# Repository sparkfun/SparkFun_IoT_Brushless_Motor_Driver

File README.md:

SparkFun IoT Brushless Motor Driver (ESP32 WROOM, TMC6300)
========================================

[*SparkFun IoT Brushless Motor Driver (ESP32 WROOM, TMC6300) (ROB-22132)*](https://www.sparkfun.com/products/22132)

The SparkFun IoT Brushless Motor Driver is an all-in-one development platform. It includes all the components to create a simple IoT device or learn about [control systems](https://en.wikipedia.org/wiki/Control_system). On the boaard, users will find an ESP32 microcontroller, a TMC6300 motor driver, a [gimbal motor](https://www.sparkfun.com/products/20441), a TMAG5273 hall-effect sensor, three INA240A1 inline current sensors, an MCP6021T low-side current sensor, two user buttons, a Qwiic connector, a 3-pin JST connector (for the gimbal motor), and a WS2812 RGB LED.

The TMC6300 from [ADI + Trinamic](https://www.trinamic.com/) is a powerful and easy-to-use three-phase motor driver with up to 2A (1.4A<sub>RMS</sub>) of total drive current. Separate high-side and low-side control of the three half-bridges allows for incredible control of each phase of the [motor commutation](https://fab.cba.mit.edu/classes/865.21/topics/power_electronics/commutation/#bldc-commutation). We've found the [*Arduino Simple Field Oriented Control*](https://docs.simplefoc.com/) library to work well with the TMC6300 motor driver.

However, a field-oriented control (FOC) algorithm requires some feedback to close and optimize the control loop. Therefore, we integrated a TMAG5273 hall-effect sensor and INA240A1 current sensor amplifiers *(both manufactured by [Texas Instruments](https://www.ti.com/))* into the design of the IoT motor driver board. This allows users to incorporate a [position sensor](https://docs.simplefoc.com/position_sensors) and [current sensing](https://docs.simplefoc.com/current_sense) into the FOC algorithm or any feedback control loop they choose to implement.

Repository Contents
-------------------

* **[/docs](/docs/)** - Online documentation files
    * [assets](/docs/assets/) - Assets files
        * [arduino_examples](/docs/assets/arduino_examples/) - Example code
        * [board_files](/docs/assets/board_files/) - Files for the product design
            * [Eagle design files](/docs/assets/board_files/eagle_files.zip) (.zip)
            * [Schematic](/docs/assets/board_files/schematic.pdf) (.pdf)
            * [Dimensions](/docs/assets/board_files/dimensions.pdf) (.pdf)
        * [component_documentation](/docs/assets/component_documentation/) - Datasheets for hardware components
        * [img/hookup_guide/](/docs/assets/img/hookup_guide/) - Images for hookup guide documentation
* **[/Hardware](/Hardware/)** - Eagle design files (.brd, .sch)
* **[/Production](/Production/)** - Production files

Documentation
--------------

* **[Hookup Guide (mkdocs)](http://docs.sparkfun.com/SparkFun_IoT_Brushless_Motor_Driver/)** - Hookup guide for the IoT Brushless Motor Driver hosted by GitHub pages.

*Need to download or print our hookup guide?*

* [Print *(Print to PDF)* from Single-Page View](http://docs.sparkfun.com/SparkFun_IoT_Brushless_Motor_Driver/print_view)

Product Variants
----------------

* [ROB-22132](https://www.sparkfun.com/products/22132)- v1.0, Initial Release

Version History
---------------

* [v10](https://github.com/sparkfun/SparkFun_IoT_Brushless_Motor_Driver/releases/tag/v10) - Initial Release

License Information
-------------------

This product is ***open source***!

Please review the [`LICENSE.md`](./LICENSE.md) file for license information.

If you have any questions or concerns about licensing, please contact technical support on our [SparkFun forums](https://forum.sparkfun.com/viewforum.php?f=152).

Distributed as-is; no warranty is given.

- Your friends at SparkFun.

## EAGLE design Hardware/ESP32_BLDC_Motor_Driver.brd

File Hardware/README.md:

SparkFun IoT Brushless Motor Driver Design Files
=====================================

The .sch and .brd files hare are Eagle CAD schematic and PCB design files from SparkFun Electronics.
A freeware version of Autodesk Eagle can be found [here](https://www.autodesk.com/products/eagle/free-download).

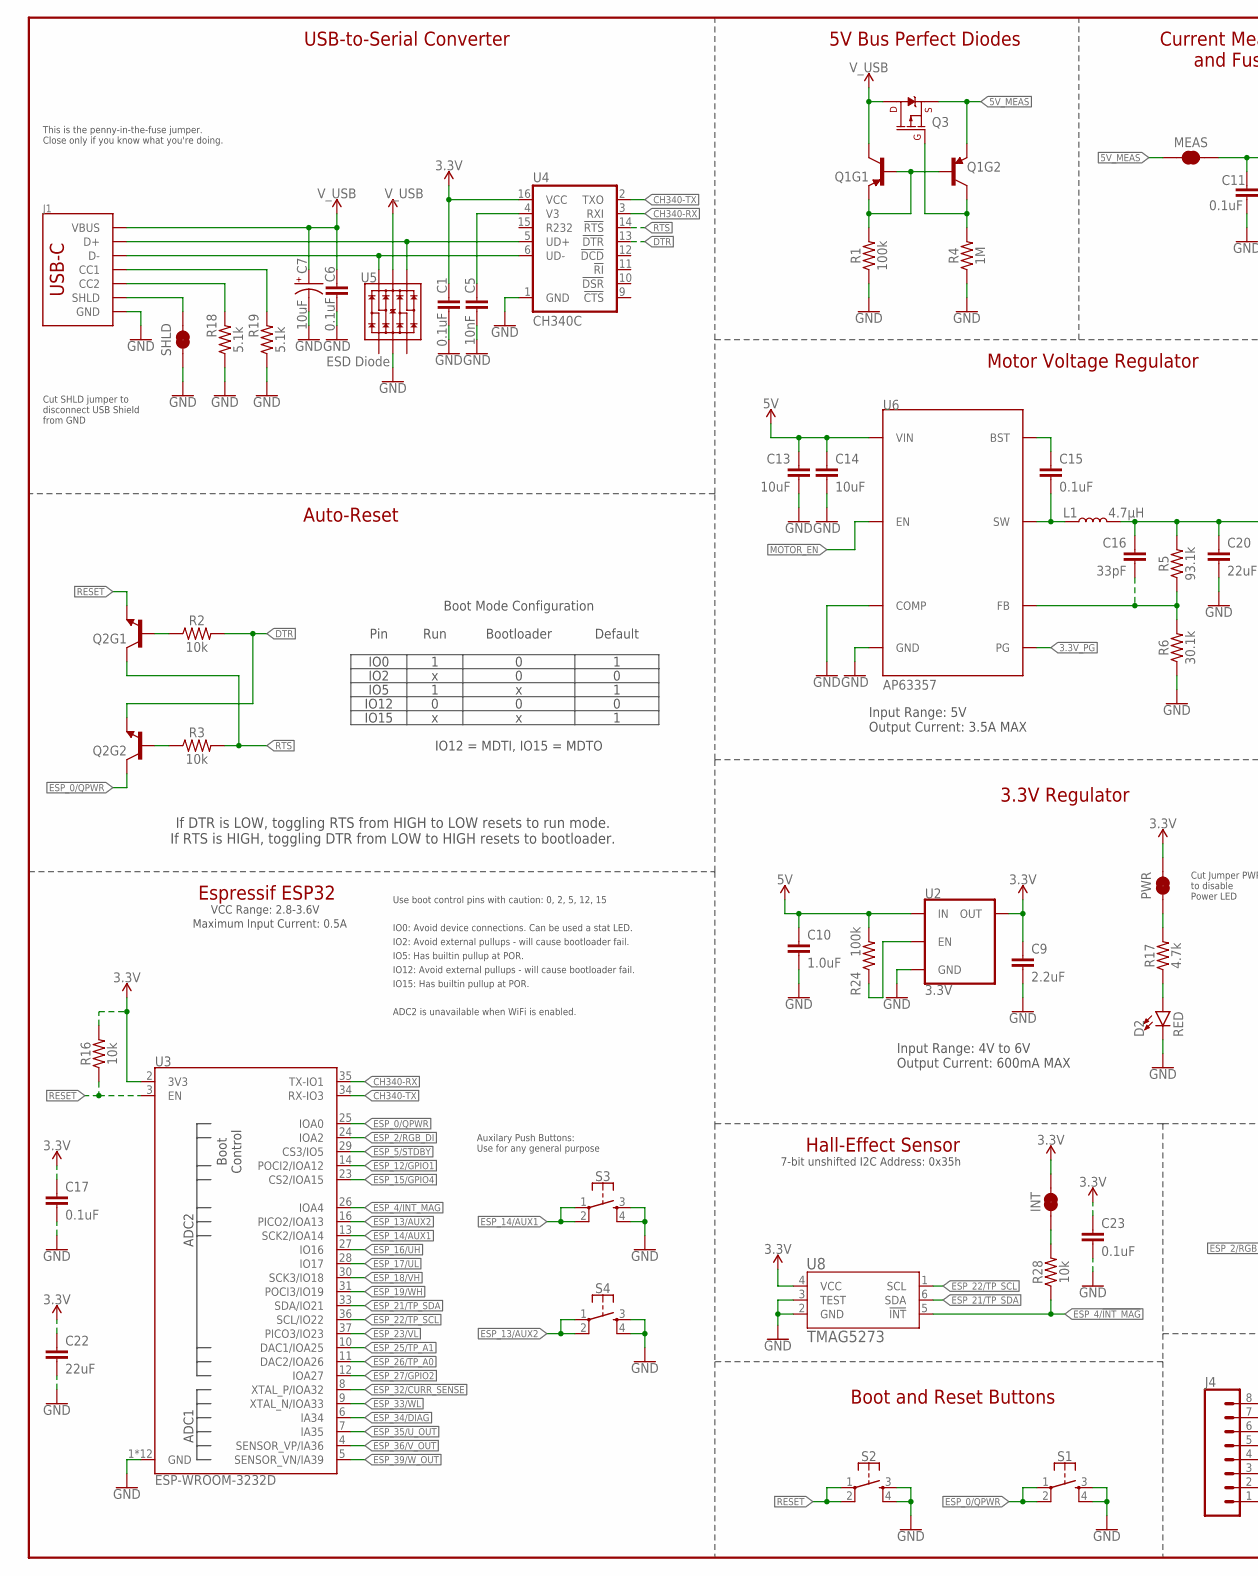
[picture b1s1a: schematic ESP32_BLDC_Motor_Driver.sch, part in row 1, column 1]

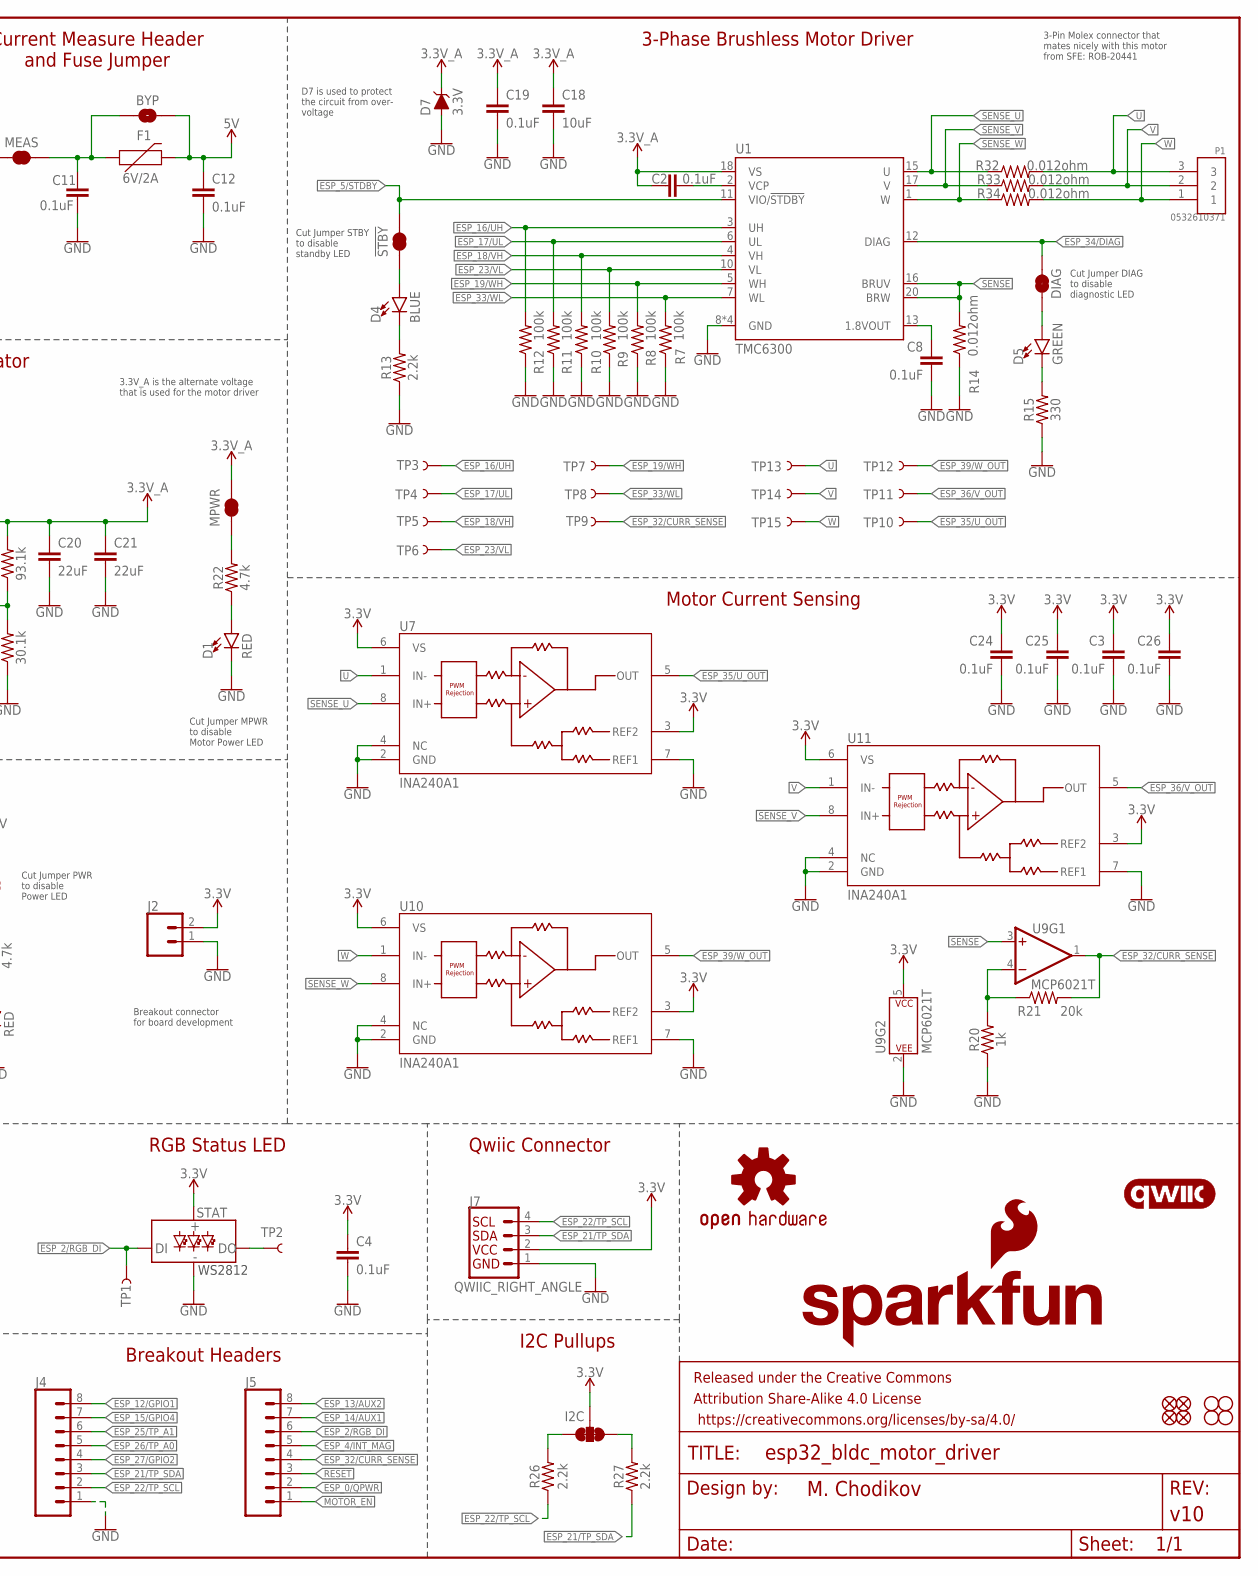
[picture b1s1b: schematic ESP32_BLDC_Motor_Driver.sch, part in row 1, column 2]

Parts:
!STBY: JUMPER-SMT_2_NC_TRACE_SILK; SMT-JUMPER_2_NC_TRACE_SILK
BYP: JUMPER-SMT_2_NO_SILK; SMT-JUMPER_2_NO_SILK
C1, C2, C3, C4, C6, C8, C11, C12, C15, C17, C19, C24, C25, C26: 0.1uF; 0603
C5: 10nF; 0603
C7: 10uF; 0603-POLAR
C9: 2.2uF; 0603
C10: 1.0uF; 0603
C13, C14, C18: 10uF; 0603
C16: 33pF; 0603
C20, C21, C22: 22uF; 0603
C23: 0.1uF; 0402
D1, D2: RED; LED-0603
D4: BLUE; LED-0603
D5: GREEN; LED-0603
D7: 3.3V; SOD-323
DIAG: JUMPER-SMT_2_NC_TRACE_SILK; SMT-JUMPER_2_NC_TRACE_SILK
F1: 6V/2A; 1210
FD1, FD2, FD3, FD4: FIDUCIALUFIDUCIAL; FIDUCIAL-MICRO
FRAME1: FRAME-LEDGER; CREATIVE_COMMONS
H1, H2, H3, H4: STAND-OFF
I2C: JUMPER-SMT_3_2-NC_TRACE_SILK; SMT-JUMPER_3_2-NC_TRACE_SILK
INT: JUMPER-SMT_2_NC_TRACE_SILK; SMT-JUMPER_2_NC_TRACE_SILK
J1: USB-C Connector; USB-C-16P_4LAYER-PADS
J2: CONN_021X02_NO_SILK; 1X02_NO_SILK
J4: Breadboard Connector; 1X08_NO_SILK
J5: Breadboard Headers; 1X08_NO_SILK
J7: QWIIC_RIGHT_ANGLE; JST04_1MM_RA
L1: 4.7μH; INDUCTOR_4X4MM
LOGO1: SFE_LOGO_NAMEBLANK; BLANK
LOGO2: OSHW-LOGOM; OSHW-LOGO-M
LOGO3: SFE_LOGO_FLAME.2_INCH; SFE_LOGO_FLAME_.2
LOGO4: QWIIC_LOGO_5MM; QWIIC_5MM
MEAS: JUMPER-COMBO_2_NC_TRACE; COMBO-JUMPER_2_NC_TRACE
MPWR: JUMPER-SMT_2_NC_TRACE_SILK; SMT-JUMPER_2_NC_TRACE_SILK
P1: 0532610371; MOLEX_0532610371
PWR: JUMPER-SMT_2_NC_TRACE_SILK; SMT-JUMPER_2_NC_TRACE_SILK
Q1: TRANS_PNP_DUALSOT-363; SOT363_PHILIPS
Q2: NPN Transistors; SC70-6
Q3: 20V/4.2A/52mΩ/1.4W; SOT23-3
R1, R7, R8, R9, R10, R11, R12, R24: 100k; 0603
R2, R3, R16, R28: 10k; 0603
R4: 1M; 0603
R5: 93.1k; 0603
R6: 30.1k; 0603
R13, R26, R27: 2.2k; 0603
R14, R32, R33, R34: 0.012ohm; 0603
R15: 330; 0603
R17, R22: 4.7k; 0603
R18, R19: 5.1k; 0603
R20: 1k; 0603
R21: 20k; 0603
S1, S2, S3, S4: MOMENTARY-SWITCH-SPST-2-SMD-5.2MM-TALL; TACTILE_SWITCH_SMD_5.2MM
SHLD: JUMPER-SMT_2_NC_TRACE_SILK; SMT-JUMPER_2_NC_TRACE_SILK
STAT: WS2812_2020; WS2812-2020
TP1, TP2, TP3, TP4, TP5, TP6, TP7, TP8, TP9, TP10, TP11, TP12, TP13, TP14, TP15: TEST-POINT3X4; PAD.03X.04
U1: TMC6300; QFN-20
U2: 3.3V; SOT23-5
U3: ESP-WROOM-3232D; ESP-WROOM-32D
U4: CH340C; SO016
U5: ESD Diode; SOT-23-6
U6: AP63357; V-DFN3020-13
U7, U10, U11: INA240A1; D8_TEX
U8: TMAG5273; SOT23-6_DBV_TEX
U9: MCP6021T; SOT23-5

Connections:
1.8_VOUT: C8.1, U1.13 (1.8VOUT)
3.3V: C1.1, C3.1, C4.1, C9.1, C17.1, C22.1, C23.1, C24.1, C25.1, C26.1, I2C.2, INT.2, J2.2, J7.2, PWR.2, R16.2, STAT.VCC, U2.5 (OUT), U3.2 (3V3), U4.16 (VCC), U7.3 (REF2), U7.6 (VS), U8.4 (VCC), U9.5 (P$V+), U10.3 (REF2), U10.6 (VS), U11.3 (REF2), U11.6 (VS)
3.3V_A: C2.1, C16.2, C18.1, C19.1, C20.1, C21.1, D7.C, L1.P$2 (2), MPWR.2, R5.2, U1.18 (VS)
3.3V_PG: U6.P$5 (PG)
5V: BYP.2, C10.1, C12.1, C13.1, C14.1, F1.2, R24.2, U2.1 (IN), U6.P$1 (VIN)
5V_MEAS: MEAS.1, MEAS.3 (1), Q1.4 (E), Q3.2 (S)
!RESET: J5.3, Q2.4 (E), R16.1, S2.1, S2.2, U3.3 (EN)
BST: C15.1, U6.P$6 (BST)
CH340-RX: U3.35 (TX-IO1), U4.3 (RXI)
CH340-TX: U3.34 (RX-IO3), U4.2 (TXO)
D: D5.A, DIAG.1
D+: J1.A6 (D+), J1.B6 (D+), U4.5 (UD+), U5.4 (IO3)
D-: J1.A7 (D-), J1.B7 (D-), U4.6 (UD-), U5.6 (IO4)
DTR: Q2.1 (E), R2.2, U4.13 (!DTR)
ESP_0/QPWR: J5.2, Q2.6 (C), S1.1, S1.2, U3.25 (IOA0)
ESP_2/RGB_DI: J5.6, STAT.DI, TP1.1, U3.24 (IOA2)
ESP_4/!INT_MAG: J5.5, R28.1, U3.26 (IOA4), U8.5 (!INT)
ESP_5/!STDBY: !STBY.2, U1.11 (VIO/!STDBY!), U3.29 (CS3/IO5)
ESP_12/GPIO1: J4.8, U3.14 (POCI2/IOA12)
ESP_13/AUX2: J5.8, S4.1, S4.2, U3.16 (PICO2/IOA13)
ESP_14/AUX1: J5.7, S3.1, S3.2, U3.13 (SCK2/IOA14)
ESP_15/GPIO4: J4.7, U3.23 (CS2/IOA15)
ESP_16/UH: R12.2, TP3.1, U1.3 (UH), U3.27 (IO16)
ESP_17/UL: R11.2, TP4.1, U1.6 (UL), U3.28 (IO17)
ESP_18/VH: R10.2, TP5.1, U1.4 (VH), U3.30 (SCK3/IO18)
ESP_19/WH: R8.2, TP7.1, U1.5 (WH), U3.31 (POCI3/IO19)
ESP_21/TP_SDA: J4.3, J7.3, R27.1, U3.33 (SDA/IO21), U8.6 (SDA)
ESP_22/TP_SCL: J4.2, J7.4, R26.1, U3.36 (SCL/IO22), U8.1 (SCL)
ESP_23/VL: R9.2, TP6.1, U1.10 (VL), U3.37 (PICO3/IO23)
ESP_25/TP_A1: J4.6, U3.10 (DAC1/IOA25)
ESP_26/TP_A0: J4.5, U3.11 (DAC2/IOA26)
ESP_27/GPIO2: J4.4, U3.12 (IOA27)
ESP_32/CURR_SENSE: J5.4, R21.2, TP9.1, U3.8 (XTAL_P/IOA32), U9.1 (OUT)
ESP_33/WL: R7.2, TP8.1, U1.7 (WL), U3.9 (XTAL_N/IOA33)
ESP_34/DIAG: DIAG.2, U1.12 (DIAG), U3.6 (IA34)
ESP_35/U_OUT: TP10.1, U3.7 (IA35), U7.5 (OUT)
ESP_36/V_OUT: TP11.1, U3.4 (SENSOR_VP/IA36), U11.5 (OUT)
ESP_39/W_OUT: TP12.1, U3.5 (SENSOR_VN/IA39), U10.5 (OUT)
FB: C16.1, R5.1, R6.2, U6.P$3 (FB)
GND: C1.2, C3.2, C4.2, C5.2, C6.2, C7.-, C8.2, C9.2, C10.2, C11.2, C12.2, C13.2, C14.2, C17.2, C18.2, C19.2, C20.2, C21.2, C22.2, C23.2, C24.2, C25.2, C26.2, D1.C, D2.C, D7.A, J1.GND, J1.GND2 (GND), J2.1, J4.1, J7.1, R1.1, R4.1, R6.1, R7.1, R8.1, R9.1, R10.1, R11.1, R12.1, R13.1, R14.1, R15.1, R18.1, R19.1, R20.1, S1.3, S1.4, S2.3, S2.4, S3.3, S3.4, S4.3, S4.4, SHLD.1, STAT.GND, U1.8 (GND), U1.9 (GND), U1.14 (GND), U1.PAD (GND), U2.2 (GND), U3.1 (GND), U3.15 (GND), U3.38 (GND), U3.GND, U3.GNDT1 (GND), U3.GNDT2 (GND), U3.GNDT3 (GND), U3.GNDT4 (GND), U3.GNDT5 (GND), U3.GNDT6 (GND), U3.GNDT7 (GND), U3.GNDT8 (GND), U4.1 (GND), U5.2 (VSS), U6.P$4 (COMP), U6.P$8 (GND), U7.2 (GND), U7.4 (NC), U7.7 (REF1), U8.2 (GND), U8.3 (TEST), U9.2 (P$V-), U10.2 (GND), U10.4 (NC), U10.7 (REF1), U11.2 (GND), U11.4 (NC), U11.7 (REF1)
MOTOR_EN: J5.1, U6.P$2 (EN)
unnamed: J1.A5 (CC1), R19.2
unnamed: C5.1, U4.4 (V3)
unnamed: J1.B5 (CC2), R18.2
unnamed: C2.2, U1.2 (VCP)
unnamed: R24.1, U2.3 (EN)
unnamed: Q2.5 (B), R2.1
unnamed: Q2.2 (B), R3.1
unnamed: D2.A, R17.1
unnamed: INT.1, R28.2
unnamed: I2C.3, R26.2
unnamed: I2C.1, R27.2
unnamed: R20.2, R21.1, U9.4 (-IN)
unnamed: PWR.1, R17.2
unnamed: BYP.1, C11.1, F1.1, MEAS.2, MEAS.4 (2)
unnamed: Q1.3 (C), Q3.1 (G), R4.2
unnamed: Q1.1 (E), Q1.2 (B), Q1.5 (B), R1.2
unnamed: D1.A, R22.1
unnamed: MPWR.1, R22.2
unnamed: D4.C, R13.2
unnamed: D5.C, R15.2
RTS: Q2.3 (C), R3.2, U4.14 (!RTS)
S: !STBY.1, D4.A
SENSE: R14.2, U1.16 (BRUV), U1.20 (BRW), U9.3 (+IN)
SENSE_U: R32.1, U1.15 (U), U7.8 (IN+)
SENSE_V: R33.1, U1.17 (V), U11.8 (IN+)
SENSE_W: R34.1, U1.1 (W), U10.8 (IN+)
SHLD: J1.SHLD1 (SHLD), J1.SHLD2 (SHLD), J1.SHLD3 (SHLD), J1.SHLD4 (SHLD), SHLD.2
SW: C15.2, L1.P$1 (1), U6.P$7 (SW), U6.P$9 (SW)
TP2: STAT.DO, TP2.1
U: P1.3, R32.2, TP13.1, U7.1 (IN-)
V: P1.2, R33.2, TP14.1, U11.1 (IN-)
V_USB: C6.1, C7.+, J1.VBUS1 (VBUS), J1.VBUS2 (VBUS), Q1.6 (C), Q3.3 (D), U5.5 (VCC)
W: P1.1, R34.2, TP15.1, U10.1 (IN-)

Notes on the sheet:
Espressif ESP32
VCC Range: 2.8-3.6V
3-Phase Brushless Motor Driver
USB-to-Serial Converter
Cut Jumper DIAG to disable diagnostic LED
Cut Jumper STBY to disable standby LED
Breakout Headers
Auto-Reset
Boot and Reset Buttons
If DTR is LOW, toggling RTS from HIGH to LOW resets to run mode. If RTS is HIGH, toggling DTR from LOW to HIGH resets to bootloader.
3.3V Regulator
3-Pin Molex connector that mates nicely with this motor from SFE: ROB-20441
Cut SHLD jumper to disconnect USB Shield from GND
This is the penny-in-the-fuse jumper. Close only if you know what you're doing.
Pin
IO0
IO2
IO12
IO15
IO5
Run
Bootloader
Default
IO12 = MDTI, IO15 = MDTO
Boot Mode Configuration
RGB Status LED
IO0: Avoid device connections. Can be used a stat LED.
ADC2 is unavailable when WiFi is enabled.
IO12: Avoid external pullups - will cause bootloader fail.
Use boot control pins with caution: 0, 2, 5, 12, 15
IO2: Avoid external pullups - will cause bootloader fail.
IO15: Has builtin pullup at POR.
IO5: Has builtin pullup at POR.
Qwiic Connector
Auxilary Push Buttons: Use for any general purpose
WS2812
Hall-Effect Sensor
Maximum Input Current: 0.5A
7-bit unshifted I2C Address: 0x35h
D7 is used to protect the circuit from over- voltage

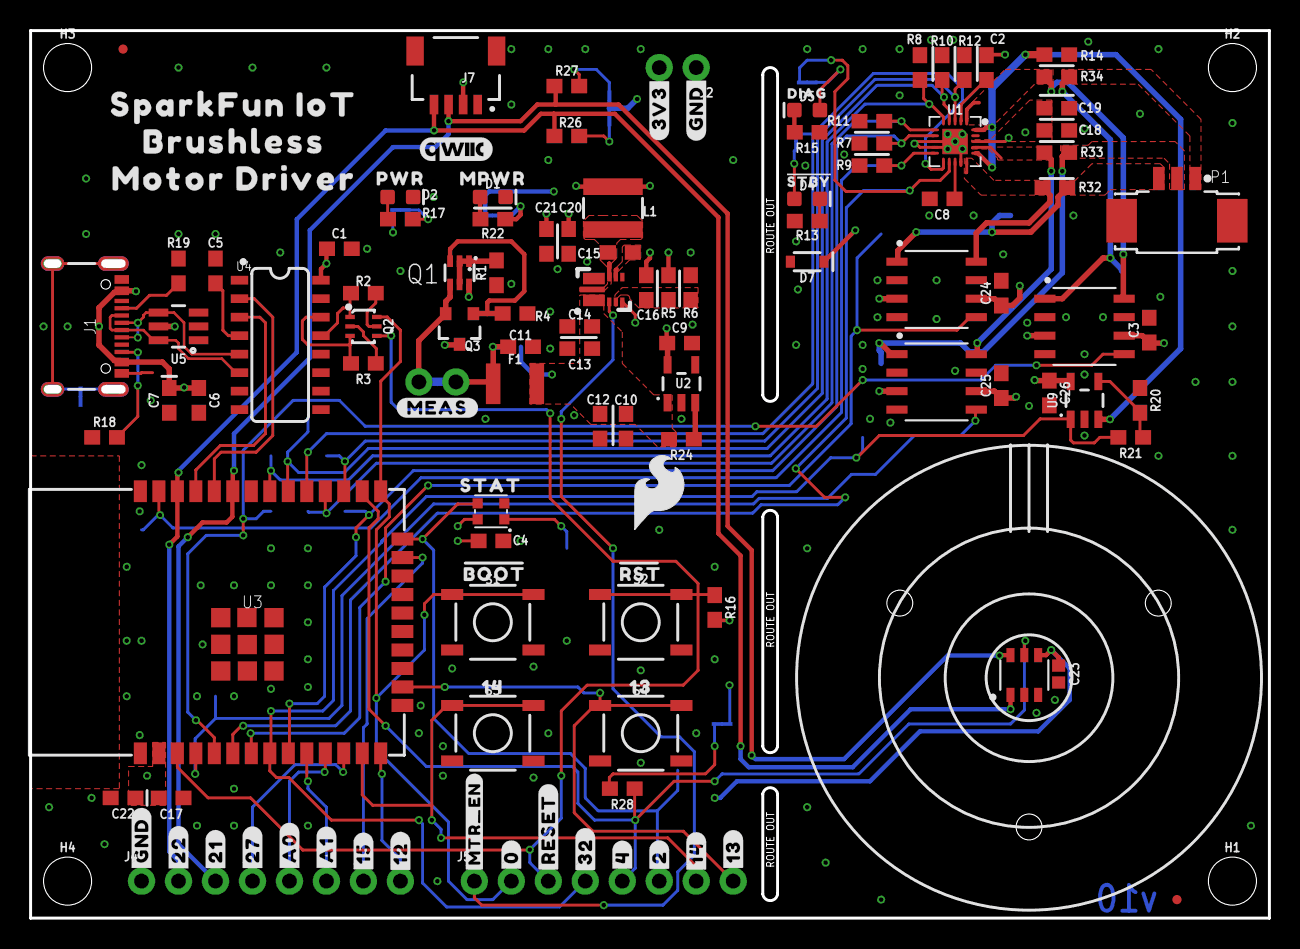
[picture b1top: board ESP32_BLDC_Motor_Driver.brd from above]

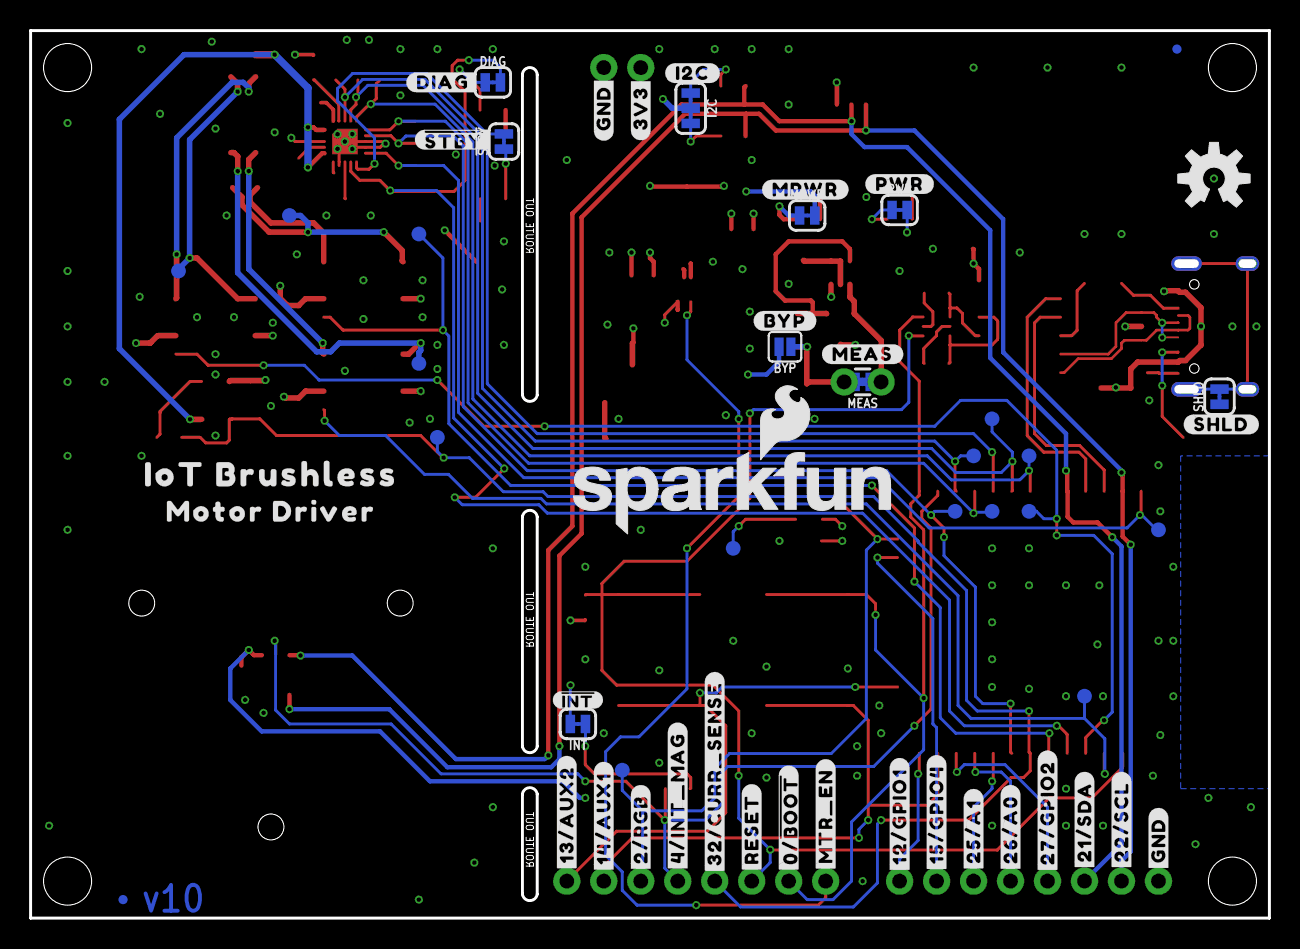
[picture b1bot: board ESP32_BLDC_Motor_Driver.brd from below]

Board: 4 copper layers, 85.1 x 61.0 mm, 187 parts (58 on the bottom side), 73 nets.

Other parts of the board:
U$1: ORDERING_INSTRUCTIONS
U$2: OT-EM3215
U$3: 1436
U$4: STAT1630063003522
U$5: RST1630063003525
U$6: #14#AUX1#36
U$7: #12#31
U$8: #DIAG#15
U$9: #14#36
U$10: ##STBY##16
U$11: BOOT21630063003532
U$12: PWR21630063003533
U$13: #MTR_EN#131458
U$14, U$15: #GND#32
U$16, U$58: #3V3#18
U$17: #4#INT_MAG#21630063003534
U$18: #22#33
U$19: #21#33
U$20: #MPWR#131468
U$21: #27#33
U$22: #15#33
U$23: #I2C#630063003467
U$24: #SHLD#630063003467
U$25: ##INT#630063003473
U$26: #32#CURR_SENSE#10
U$27: #PWR#33
U$28, U$60: #GND#17
U$29, U$30: #RESET#34
U$31: #0#33
U$32: #0##BOOT##0
U$33: #32#33
U$34: #4#33
U$35: #12#GPIO1#4
U$36: #2#33
U$37: #15#GPIO4#13
U$38: #13#36
U$39: 131437
U$40: #26#A0#30
U$41: #25#A1#30
U$42: #A1#30
U$43: #BYP#131439
U$44: SPARKFUN_IOT131442
U$45: SFE_LOGO_NAME_FLAME_.2
U$46: BRUSHLESS131445
U$47: MOTOR_DRIVER131446
U$48, U$50: #MEAS#131453
U$49: MPWR131449
U$51: #MTR_EN#131460
U$52: #13#AUX2#14
U$53: #STBY#131470
U$54: #27#GPIO2#27
U$55: IOT_BRUSHLESS131454
U$56: #21#SDA#29
U$57: DIAG131469
U$59: #2#RGB#18
U$62: MOTOR_DRIVER630063003515
U$63: #22#SCL#30
U$64: #A0#30

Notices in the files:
parts and their libraries:
SparkFun-Jumpers: Licensing: Creative Commons ShareAlike 4.0 International - https://creativecommons.org/licenses/by-sa/4.0
SparkFun-Aesthetics: Released under the Creative Commons Attribution Share-Alike 4.0 License
SparkFun-Aesthetics: Released under the Creative Commons
